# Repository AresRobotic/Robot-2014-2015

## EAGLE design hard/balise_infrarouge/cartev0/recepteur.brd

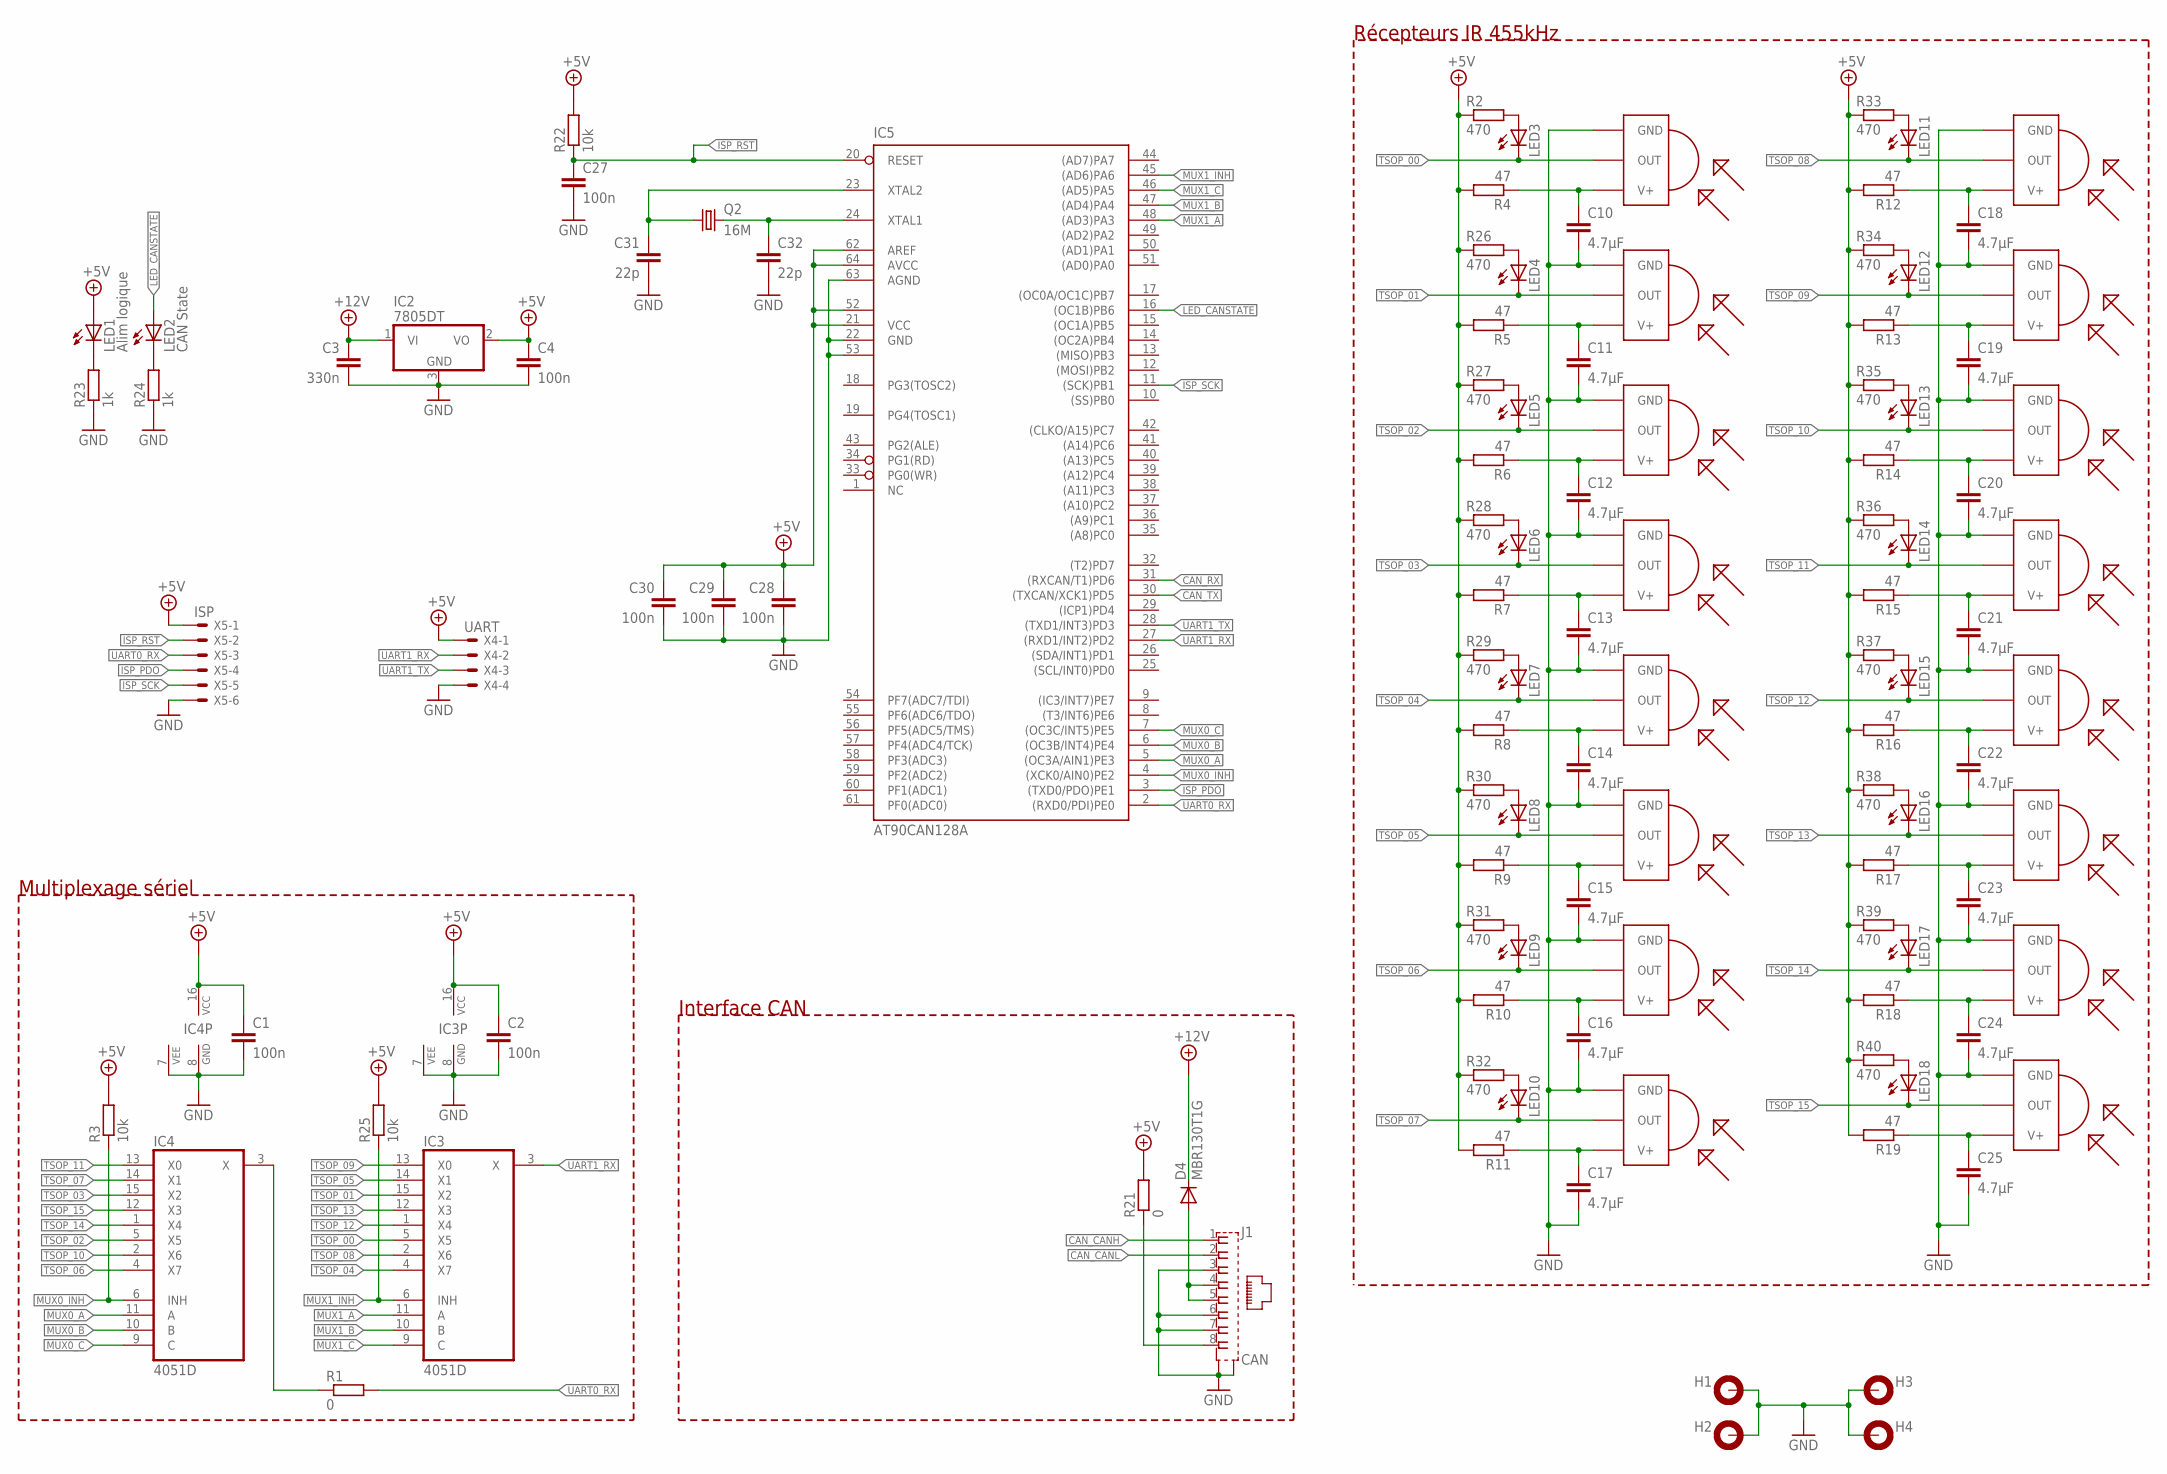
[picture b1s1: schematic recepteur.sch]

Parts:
C1, C2, C4, C27, C28, C29, C30: 100n; C0805
C3: 330n; C0805
C10, C11, C12, C13, C14, C15, C16, C17, C18, C19, C20, C21, C22, C23, C24, C25: 4.7µF; C0805
C31, C32: 22p; C0805
D4: MBR130T1G; SOD123
H1, H2, H3, H4: MOUNT-PAD-ROUND3.0; 3,0-PAD
IC2: 7805DT; TO252
IC3, IC4: 4051D; SO16
IC5: AT90CAN128A; TQFP64
J1: CAN; 557969-1
LED1: Alim logique; CHIP-LED0805
LED2: CAN State; CHIP-LED0805
LED3, LED4, LED5, LED6, LED7, LED8, LED9, LED10, LED11, LED12, LED13, LED14, LED15, LED16, LED17, LED18: LEDCHIP-LED0805; CHIP-LED0805
Q2: 16M; HC49UP
R1: 0; R0805
R2, R26, R27, R28, R29, R30, R31, R32, R33, R34, R35, R36, R37, R38, R39, R40: 470; R0805
R3, R22, R25: 10k; R0805
R4, R5, R6, R7, R8, R9, R10, R11, R12, R13, R14, R15, R16, R17, R18, R19: 47; R0805
R21: 0; M0805
R23, R24: 1k; M0805
TSOP00, TSOP01, TSOP02, TSOP03, TSOP04, TSOP05, TSOP06, TSOP07, TSOP08, TSOP09, TSOP10, TSOP11, TSOP12, TSOP13, TSOP14, TSOP15: TSOP7000; TSOP18XX
X4: UART; 53261-04
X5: ISP; 53261-06

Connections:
+5V: C1.1, C2.1, C4.1, C28.1, C29.1, C30.1, IC2.2 (VO), IC3.16 (VCC), IC4.16 (VCC), IC5.21 (VCC), IC5.52 (VCC1), IC5.62 (AREF), IC5.64 (AVCC), LED1.A, R2.1, R3.2, R4.2, R5.2, R6.2, R7.2, R8.2, R9.2, R10.2, R11.2, R12.2, R13.2, R14.2, R15.2, R16.2, R17.2, R18.2, R19.2, R21.2, R22.2, R25.2, R26.1, R27.1, R28.1, R29.1, R30.1, R31.1, R32.1, R33.1, R34.1, R35.1, R36.1, R37.1, R38.1, R39.1, R40.1, X4.1, X5.1
+12V: C3.1, D4.C, IC2.1 (VI)
CAN_CANH: J1.1
CAN_CANL: J1.2
CAN_RX: IC5.31 ((RXCAN/T1)PD6)
CAN_TX: IC5.30 ((TXCAN/XCK1)PD5)
GND: C1.2, C2.2, C3.2, C4.2, C10.2, C11.2, C12.2, C13.2, C14.2, C15.2, C16.2, C17.2, C18.2, C19.2, C20.2, C21.2, C22.2, C23.2, C24.2, C25.2, C27.2, C28.2, C29.2, C30.2, C31.2, C32.2, H1.B3,0, H2.B3,0, H3.B3,0, H4.B3,0, IC2.3 (GND), IC3.7 (VEE), IC3.8 (GND), IC4.7 (VEE), IC4.8 (GND), IC5.22 (GND), IC5.53 (GND1), IC5.63 (AGND), J1.3, J1.6, J1.7, J1.G1 (S2), J1.G2 (S1), R23.1, R24.1, TSOP00.GND, TSOP01.GND, TSOP02.GND, TSOP03.GND, TSOP04.GND, TSOP05.GND, TSOP06.GND, TSOP07.GND, TSOP08.GND, TSOP09.GND, TSOP10.GND, TSOP11.GND, TSOP12.GND, TSOP13.GND, TSOP14.GND, TSOP15.GND, X4.4, X5.6
ISP_PDO: IC5.3 ((TXD0/PDO)PE1), X5.4
ISP_RST: C27.1, IC5.20 (RESET), R22.1, X5.2
ISP_SCK: IC5.11 ((SCK)PB1), X5.5
LED_CANSTATE: IC5.16 ((OC1B)PB6), LED2.A
MUX0_A: IC4.11 (A), IC5.5 ((OC3A/AIN1)PE3)
MUX0_B: IC4.10 (B), IC5.6 ((OC3B/INT4)PE4)
MUX0_C: IC4.9 (C), IC5.7 ((OC3C/INT5)PE5)
MUX0_INH: IC4.6 (INH), IC5.4 ((XCK0/AIN0)PE2), R3.1
MUX1_A: IC3.11 (A), IC5.48 ((AD3)PA3)
MUX1_B: IC3.10 (B), IC5.47 ((AD4)PA4)
MUX1_C: IC3.9 (C), IC5.46 ((AD5)PA5)
MUX1_INH: IC3.6 (INH), IC5.45 ((AD6)PA6), R25.1
unnamed: IC4.3 (X), R1.1
unnamed: LED3.A, R2.2
unnamed: LED4.A, R26.2
unnamed: LED5.A, R27.2
unnamed: LED6.A, R28.2
unnamed: LED7.A, R29.2
unnamed: J1.8, R21.1
unnamed: C10.1, R4.1, TSOP00.VCC (V+)
unnamed: C11.1, R5.1, TSOP01.VCC (V+)
unnamed: C12.1, R6.1, TSOP02.VCC (V+)
unnamed: C13.1, R7.1, TSOP03.VCC (V+)
unnamed: C32.1, IC5.24 (XTAL1), Q2.2
unnamed: C31.1, IC5.23 (XTAL2), Q2.1
unnamed: LED1.C, R23.2
unnamed: LED8.A, R30.2
unnamed: LED2.C, R24.2
unnamed: LED9.A, R31.2
unnamed: LED10.A, R32.2
unnamed: LED11.A, R33.2
unnamed: C14.1, R8.1, TSOP04.VCC (V+)
unnamed: C15.1, R9.1, TSOP05.VCC (V+)
unnamed: C16.1, R10.1, TSOP06.VCC (V+)
unnamed: LED12.A, R34.2
unnamed: LED13.A, R35.2
unnamed: LED14.A, R36.2
unnamed: LED15.A, R37.2
unnamed: LED16.A, R38.2
unnamed: LED17.A, R39.2
unnamed: LED18.A, R40.2
unnamed: C17.1, R11.1, TSOP07.VCC (V+)
unnamed: C25.1, R19.1, TSOP15.VCC (V+)
unnamed: D4.A, J1.4, J1.5
unnamed: C24.1, R18.1, TSOP14.VCC (V+)
unnamed: C23.1, R17.1, TSOP13.VCC (V+)
unnamed: C22.1, R16.1, TSOP12.VCC (V+)
unnamed: C21.1, R15.1, TSOP11.VCC (V+)
unnamed: C19.1, R13.1, TSOP09.VCC (V+)
unnamed: C20.1, R14.1, TSOP10.VCC (V+)
unnamed: C18.1, R12.1, TSOP08.VCC (V+)
TSOP_00: IC3.5 (X5), LED3.C, TSOP00.OUT
TSOP_01: IC3.15 (X2), LED4.C, TSOP01.OUT
TSOP_02: IC4.5 (X5), LED5.C, TSOP02.OUT
TSOP_03: IC4.15 (X2), LED6.C, TSOP03.OUT
TSOP_04: IC3.4 (X7), LED7.C, TSOP04.OUT
TSOP_05: IC3.14 (X1), LED8.C, TSOP05.OUT
TSOP_06: IC4.4 (X7), LED9.C, TSOP06.OUT
TSOP_07: IC4.14 (X1), LED10.C, TSOP07.OUT
TSOP_08: IC3.2 (X6), LED11.C, TSOP08.OUT
TSOP_09: IC3.13 (X0), LED12.C, TSOP09.OUT
TSOP_10: IC4.2 (X6), LED13.C, TSOP10.OUT
TSOP_11: IC4.13 (X0), LED14.C, TSOP11.OUT
TSOP_12: IC3.1 (X4), LED15.C, TSOP12.OUT
TSOP_13: IC3.12 (X3), LED16.C, TSOP13.OUT
TSOP_14: IC4.1 (X4), LED17.C, TSOP14.OUT
TSOP_15: IC4.12 (X3), LED18.C, TSOP15.OUT
UART0_RX: IC5.2 ((RXD0/PDI)PE0), R1.2, X5.3
UART1_RX: IC3.3 (X), IC5.27 ((RXD1/INT2)PD2), X4.2
UART1_TX: IC5.28 ((TXD1/INT3)PD3), X4.3

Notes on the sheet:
Interface CAN
Multiplexage sériel
Récepteurs IR 455kHz

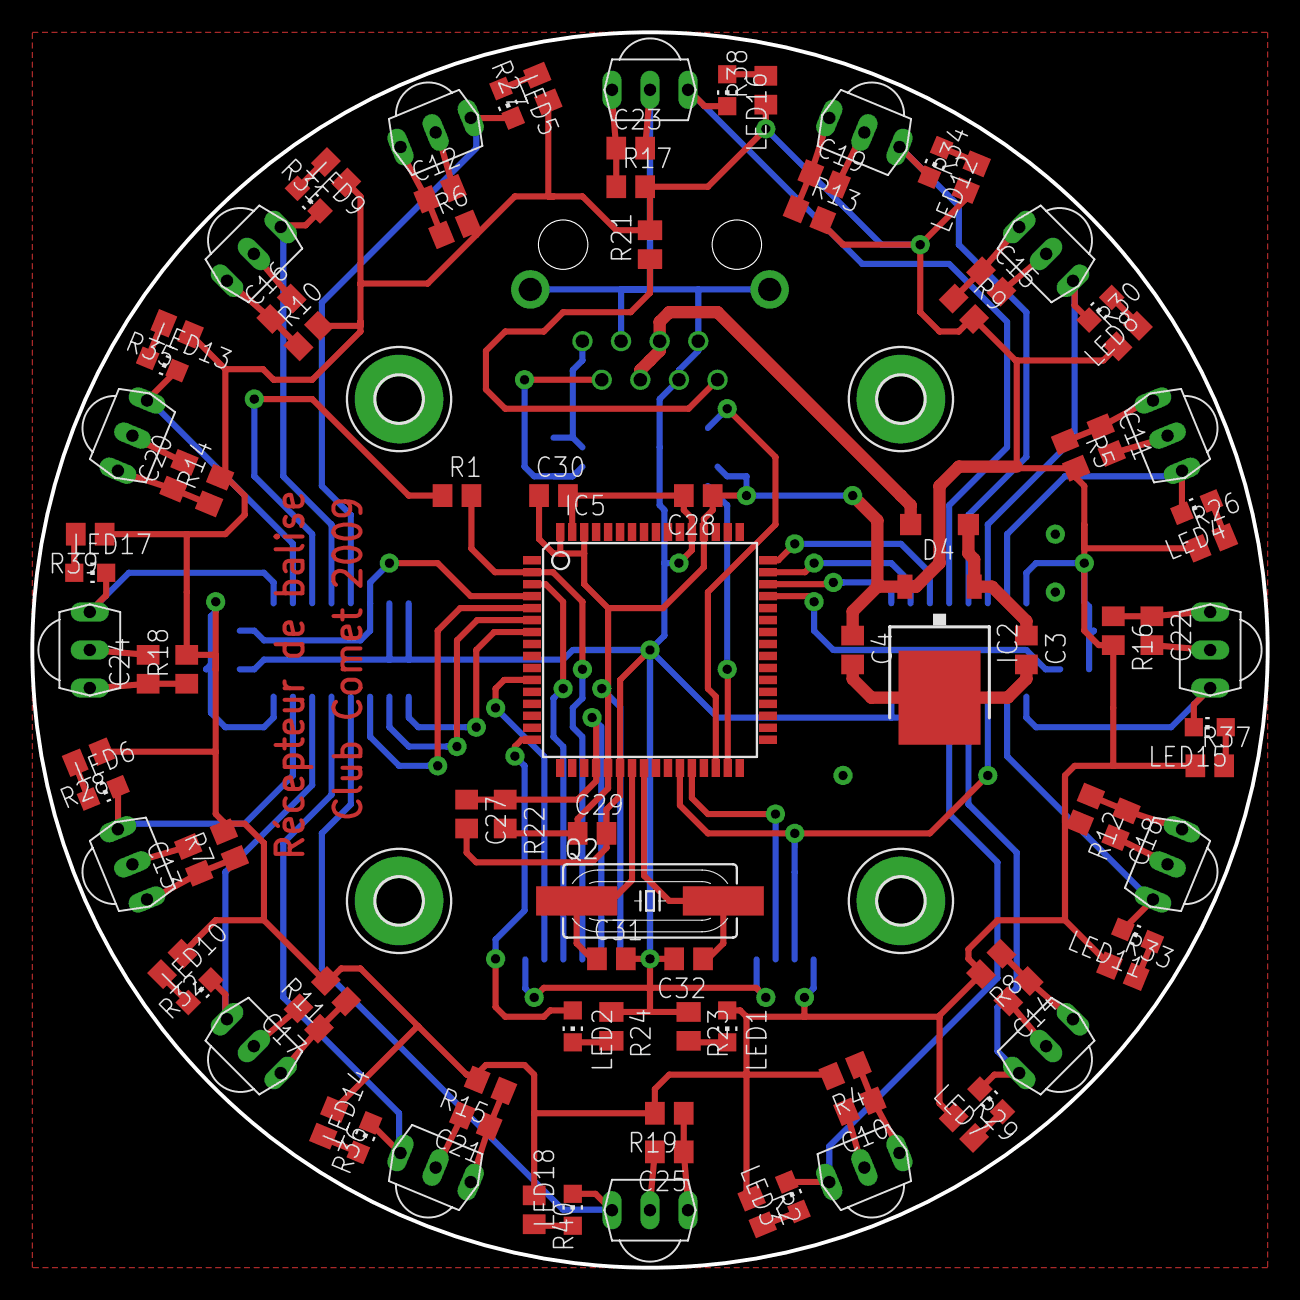
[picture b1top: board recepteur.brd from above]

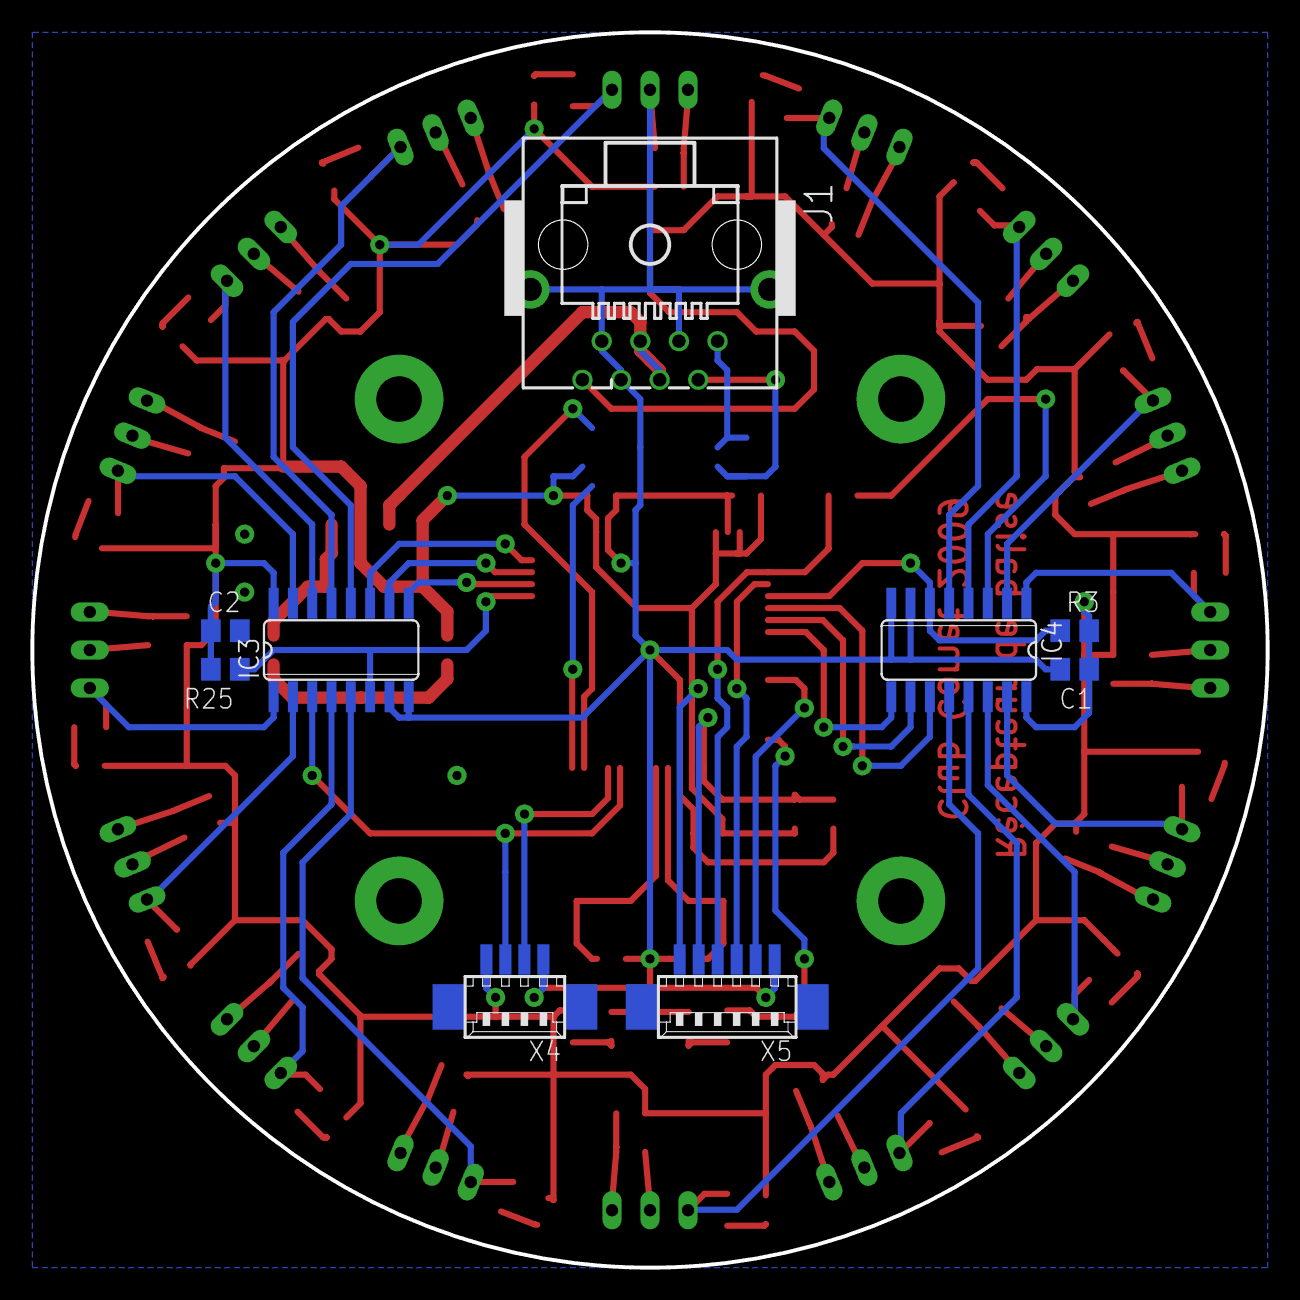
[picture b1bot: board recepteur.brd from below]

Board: 2 copper layers, 81.3 x 81.3 mm, 112 parts (9 on the bottom side), 73 nets.

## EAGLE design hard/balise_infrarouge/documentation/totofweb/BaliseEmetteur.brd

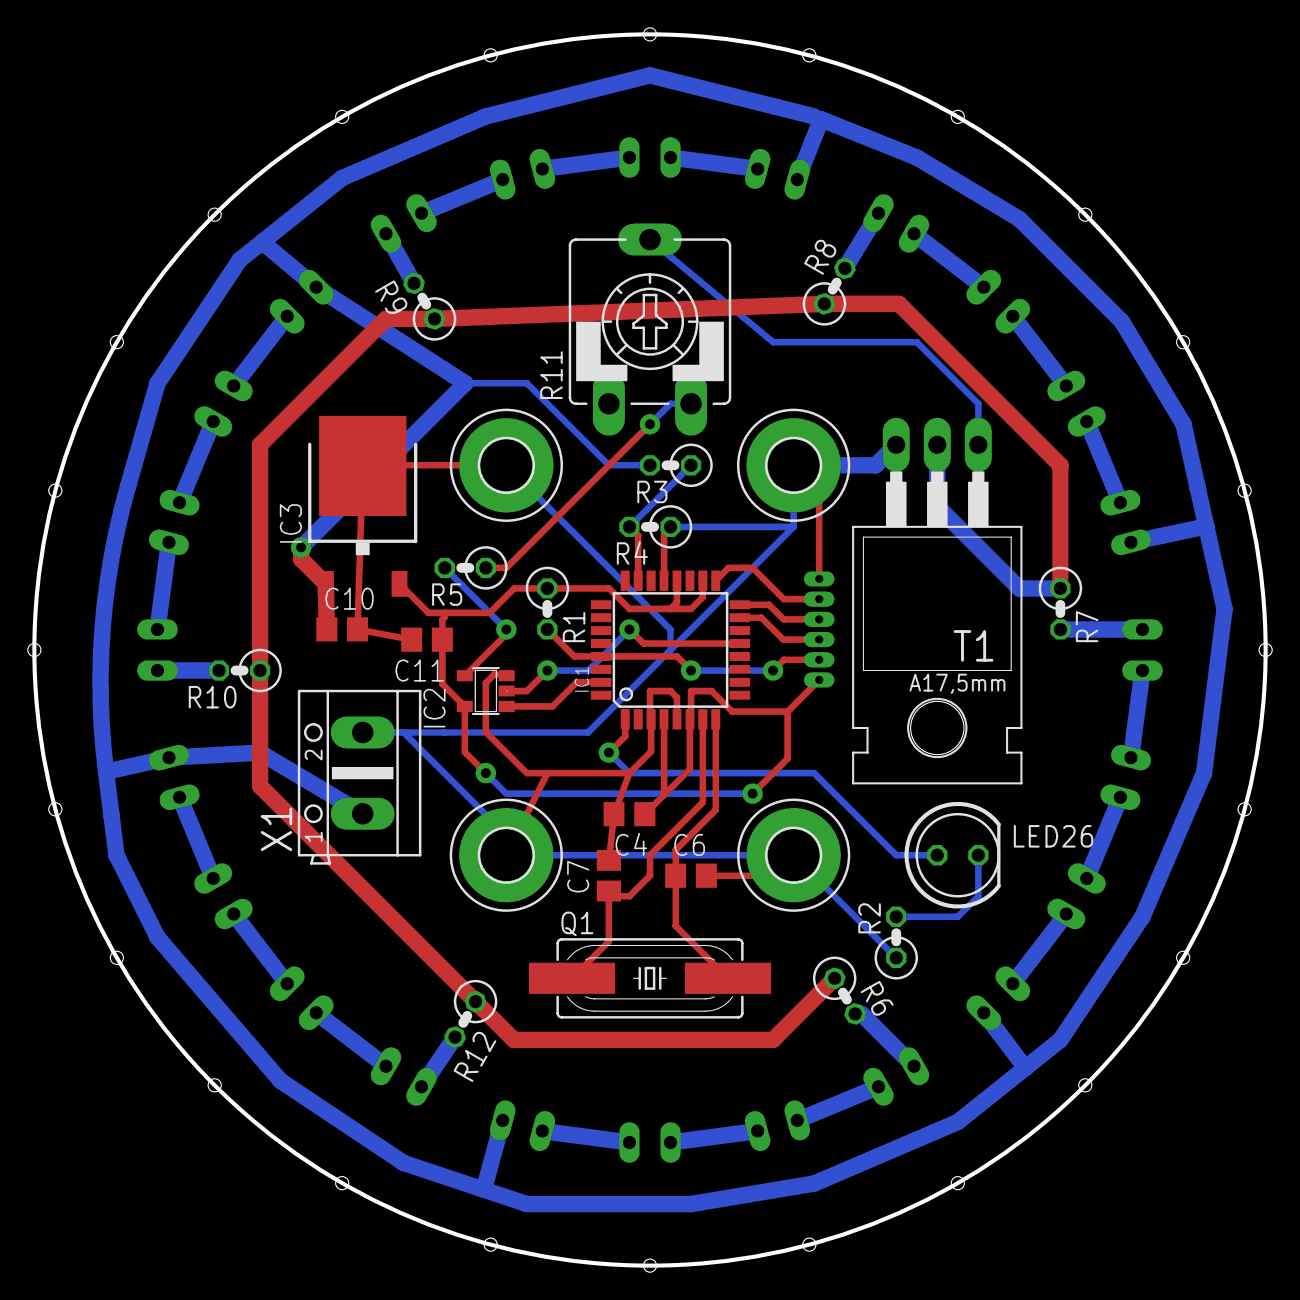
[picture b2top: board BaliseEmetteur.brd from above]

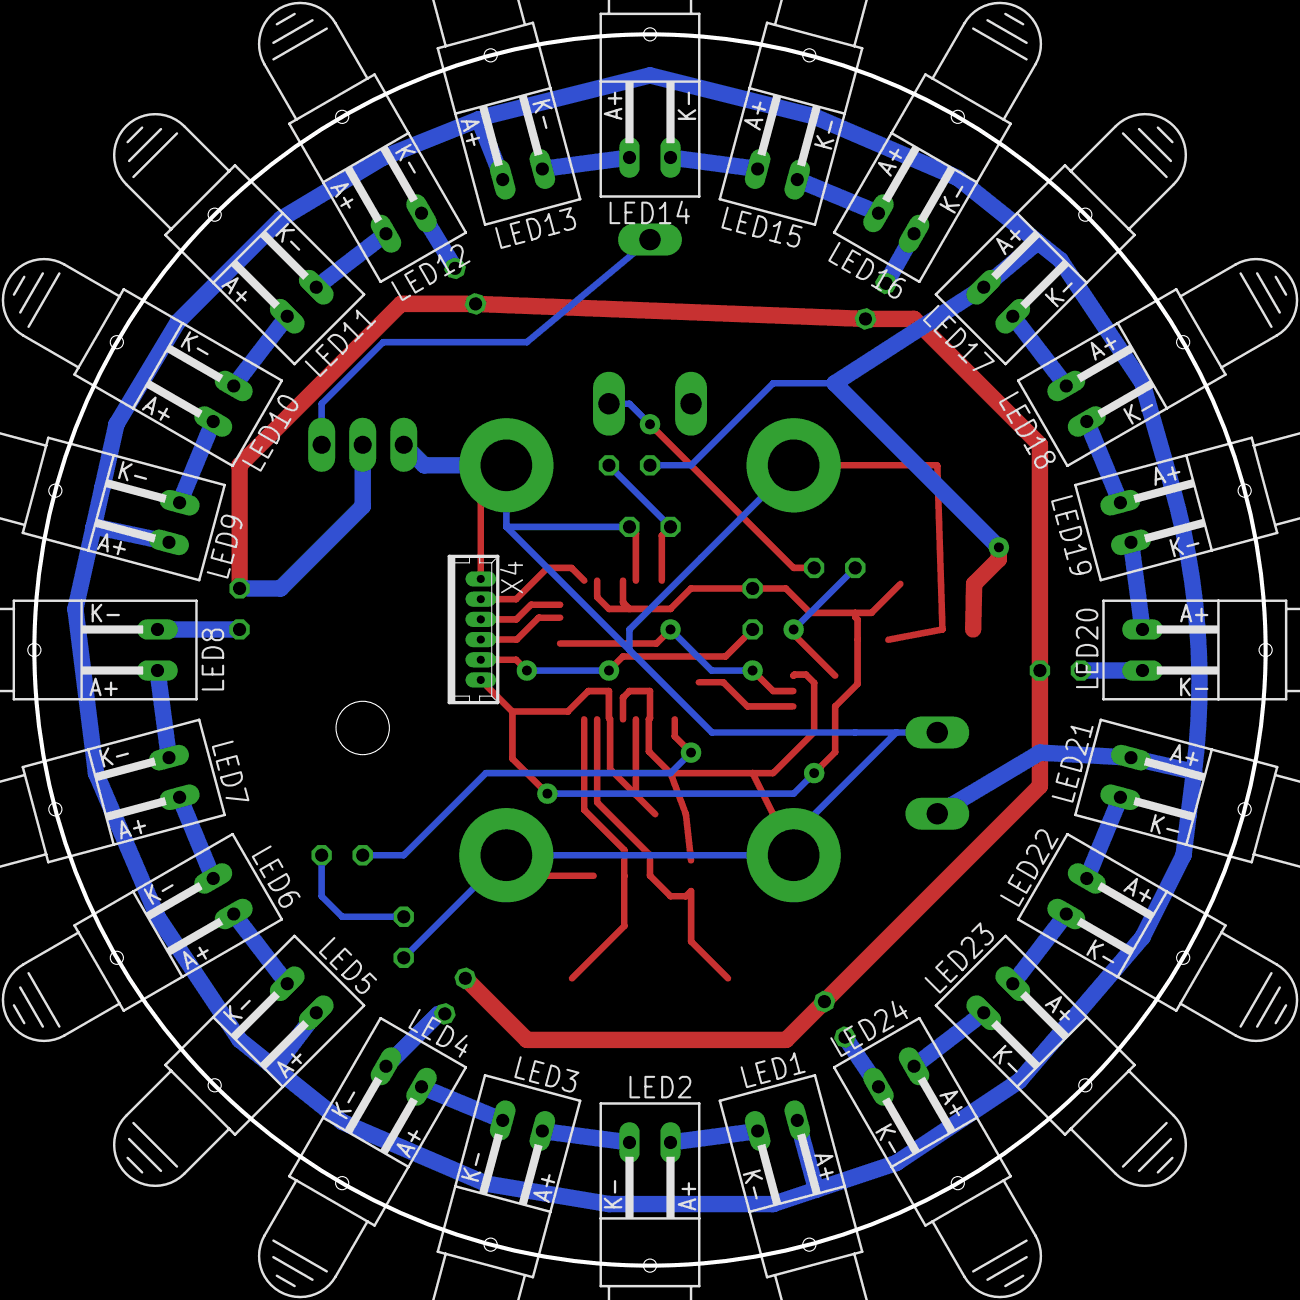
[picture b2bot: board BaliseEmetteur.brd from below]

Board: 2 copper layers, 76.2 x 76.2 mm, 53 parts (25 on the bottom side), 42 nets.

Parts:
C4: 100nF; C0805
C6, C7: 22pF; C0805
C10: 330n; C0805
C11: 100n; C0805
H1, H2, H3, H4: 3,2-PAD
IC1: MEGA8-AI; TQFP32-08
IC2: 74AHC1G02DBV; SOT23-5
IC3: 7805DT; TO252
LED1, LED2, LED3, LED4, LED5, LED6, LED7, LED8, LED9, LED10, LED11, LED12, LED13, LED14, LED15, LED16, LED17, LED18, LED19, LED20, LED21, LED22, LED23, LED24: Q62902-B155
LED26: LED5MM
Q1: 16MHz; HC49UP
R1, R3, R4: 10k; 0207/2V
R2: 470; 0207/2V
R5: 4k7; 0207/2V
R6, R7, R8, R9, R10, R12: 10; 0207/2V
R11: 220k; CA9V
T1: TIP122; TO220
X1: ALIM; AK500/2
X4: ISP; 53047-06

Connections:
+5V: C4.1, C11.1, IC1.4, IC1.6, IC1.18, IC1.20, IC2.5, IC3.2, R1.1, X4.1
+12V: C10.1, IC3.1, LED1.A, LED5.A, LED9.A, LED13.A, LED17.A, LED21.A, R3.2, X1.1
BATT_ADC: IC1.23, R3.1, R4.2
GND: C4.2, C6.2, C7.2, C10.2, C11.2, H1.B3,2, H2.B3,2, H3.B3,2, H4.B3,2, IC1.3, IC1.5, IC1.21, IC2.3, IC3.3, R2.1, R4.1, T1.3, X1.2, X4.6
ISP_MISO: IC1.16, X4.4
ISP_MOSI: IC1.15, X4.3
ISP_RST: IC1.29, R1.2, X4.2
ISP_SCK: IC1.17, X4.5
unnamed: LED26.K, R2.2
unnamed: LED1.K, LED2.A
unnamed: R5.1, R11.E
unnamed: IC1.1, LED26.A
unnamed: LED3.K, LED4.A
unnamed: LED6.K, LED7.A
unnamed: LED5.K, LED6.A
unnamed: C7.1, IC1.7, Q1.1
unnamed: C6.1, IC1.8, Q1.2
unnamed: LED7.K, LED8.A
unnamed: LED18.K, LED19.A
unnamed: LED9.K, LED10.A
unnamed: LED2.K, LED3.A
unnamed: LED11.K, LED12.A
unnamed: LED13.K, LED14.A
unnamed: R6.1, R7.1, R8.1, R9.1, R10.1, R12.1, T1.2
unnamed: LED15.K, LED16.A
unnamed: LED22.K, LED23.A
unnamed: LED17.K, LED18.A
unnamed: LED19.K, LED20.A
unnamed: LED4.K, R6.2
unnamed: LED21.K, LED22.A
unnamed: LED10.K, LED11.A
unnamed: LED23.K, LED24.A
unnamed: LED8.K, R7.2
unnamed: LED14.K, LED15.A
unnamed: LED12.K, R8.2
unnamed: LED16.K, R9.2
unnamed: R11.S, T1.1
unnamed: LED20.K, R10.2
unnamed: LED24.K, R12.2
unnamed: IC2.4, R5.2
PWM: IC1.13, IC2.2
UART_TX: IC1.31, IC2.1

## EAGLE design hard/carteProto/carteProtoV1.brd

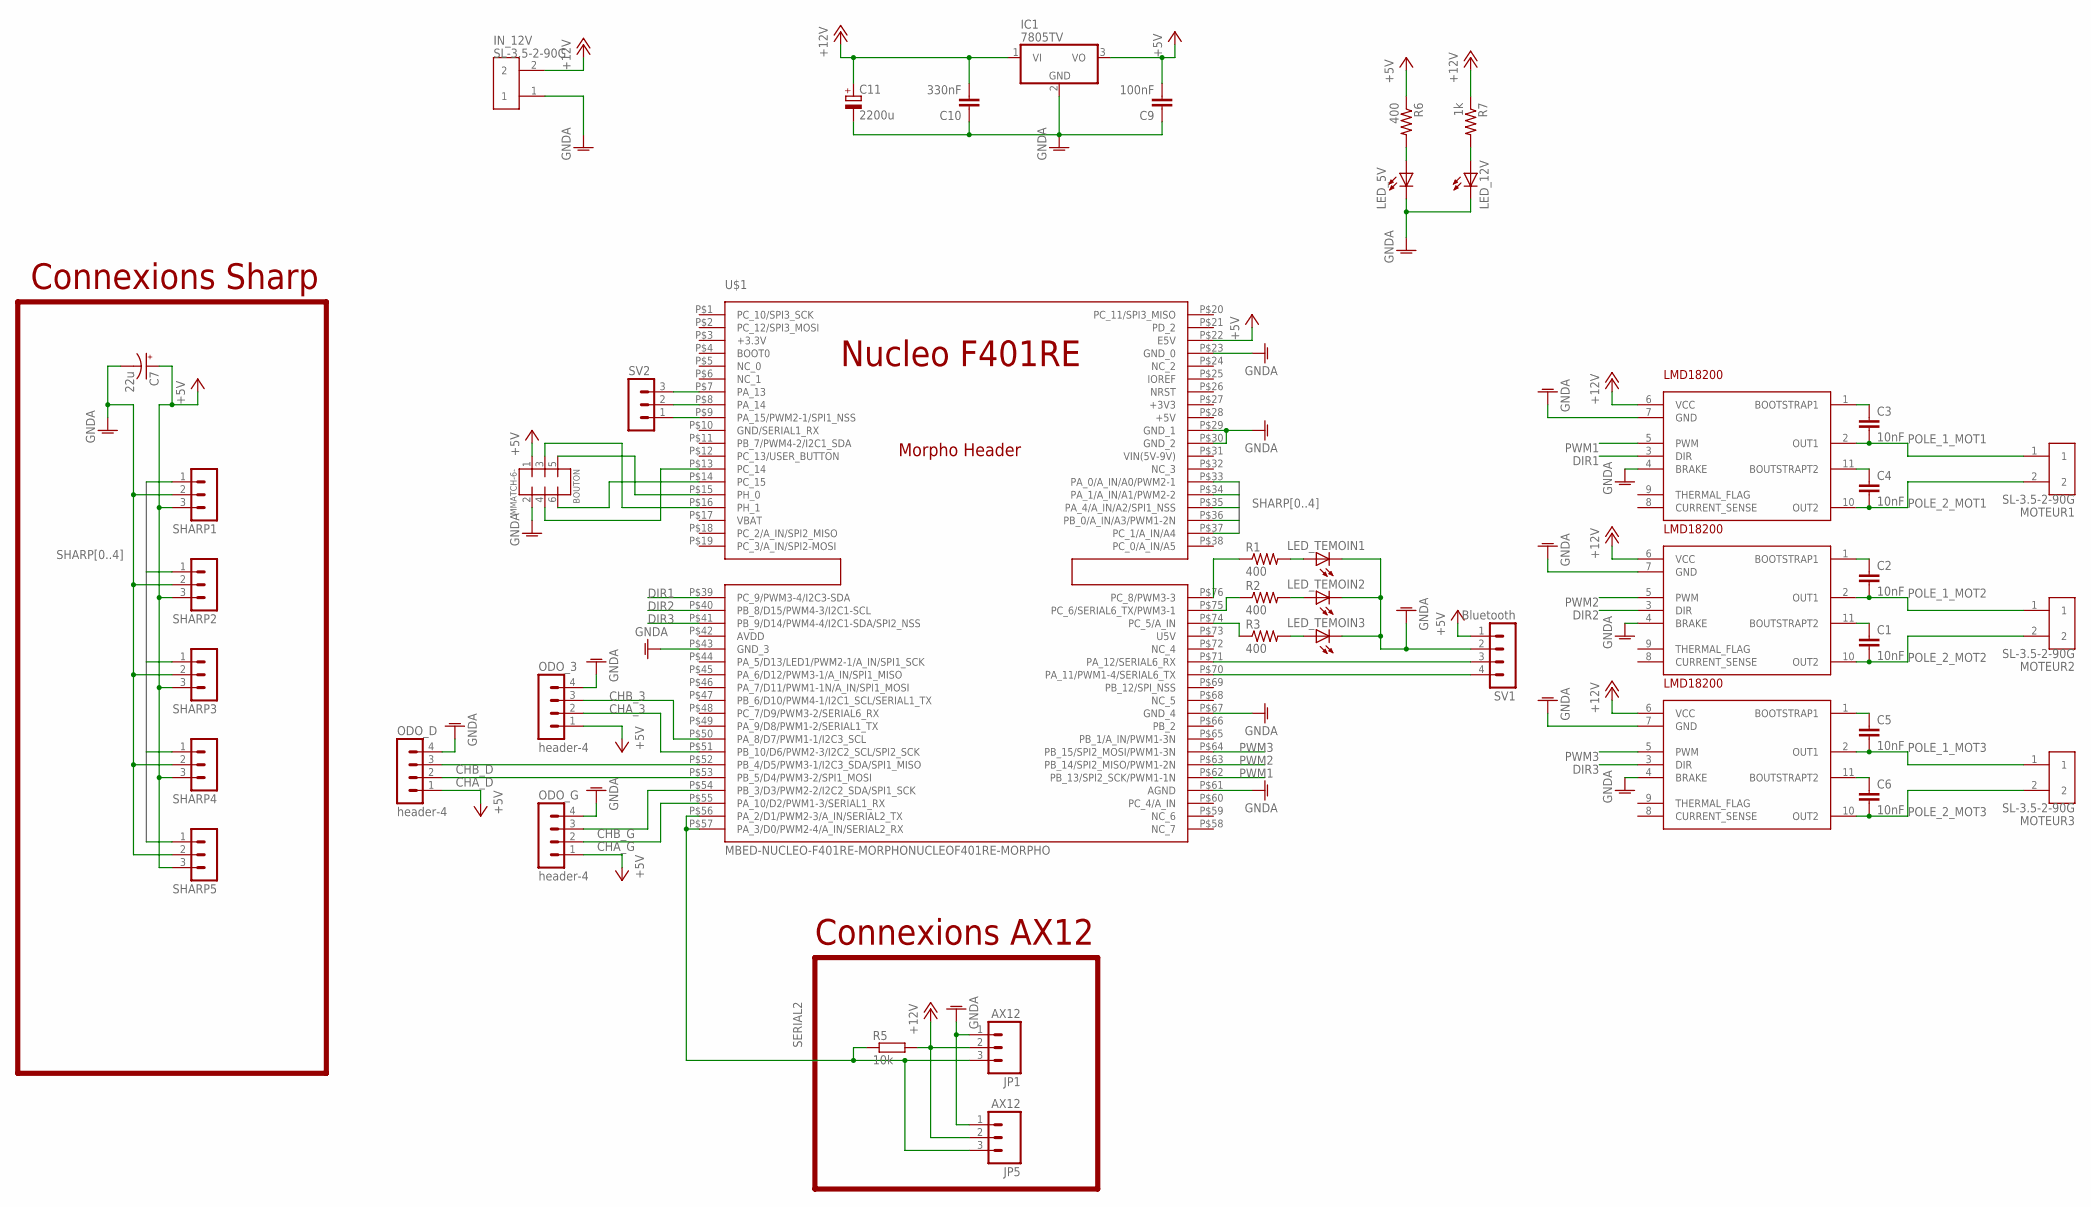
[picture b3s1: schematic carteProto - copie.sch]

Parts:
BOUTON: MMATCH-6-; AMP-215079-6
C1, C2, C3, C4, C5, C6: 10nF; C0805
C7: 22u; CPOL-RADIAL-100UF-25V
C9: 100nF; C0805
C10: 330nF; C0805
C11: 2200u; TT5D11
IC1: 7805TV; TO220V
IN_12V: SL-3.5-2-90G
JP1, JP5: AX12; MOLEX-1X3
LED_5V, LED_12V: LEDCHIPLED_0805; CHIPLED_0805
LED_TEMOIN1, LED_TEMOIN2, LED_TEMOIN3: LEDCHIPLED_0805; CHIPLED_0805
MOTEUR1, MOTEUR2, MOTEUR3: SL-3.5-2-90G
ODO_3: header-4; MA04-1
ODO_D: header-4; MA04-1
ODO_G: header-4; MA04-1
R1, R2, R3, R6: 400; 0805
R5: 10k; M0805
R7: 1k; 0805
SHARP1, SHARP2, SHARP3, SHARP4, SHARP5: MA03-1
SV1: Bluetooth; MA04-1
SV2: MA03-1
U$1: MBED-NUCLEO-F401RE-MORPHONUCLEOF401RE-MORPHO; MORPHO-HEADERS
U$2, U$3, U$4: LMD18200

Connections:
+5V: BOUTON.1 (3), C7.1 (+), C9.2, IC1.3 (VO), ODO_3.1, ODO_D.1, ODO_G.1, R6.1, SHARP1.3, SHARP2.3, SHARP3.3, SHARP4.3, SHARP5.3, SV1.1, U$1.P$22 (E5V); also elsewhere on the board
CHA_3: ODO_3.2, U$1.P$51 (PB_10/D6/PWM2-3/I2C2_SCL/SPI2_SCK)
CHA_D: ODO_D.2, U$1.P$53 (PB_5/D4/PWM3-2/SPI1_MOSI)
CHA_G: ODO_G.2, U$1.P$55 (PA_10/D2/PWM1-3/SERIAL1_RX)
CHB_3: ODO_3.3, U$1.P$50 (PA_8/D7/PWM1-1/I2C3_SCL)
CHB_D: ODO_D.3, U$1.P$52 (PB_4/D5/PWM3-1/I2C3_SDA/SPI1_MISO)
CHB_G: ODO_G.3, U$1.P$54 (PB_3/D3/PWM2-2/I2C2_SDA/SPI1_SCK)
DIR1: U$1.P$39 (PC_9/PWM3-4/I2C3-SDA), U$2.3 (DIR)
DIR2: U$1.P$40 (PB_8/D15/PWM4-3/I2C1-SCL), U$3.3 (DIR)
DIR3: U$1.P$41 (PB_9/D14/PWM4-4/I2C1-SDA/SPI2_NSS), U$4.3 (DIR)
GNDA: BOUTON.2 (4), C7.2 (-), C9.1, C10.1, C11.-, IC1.2 (GND), IN_12V.1, JP1.1, JP5.1, LED_5V.C, LED_12V.C, LED_TEMOIN1.C, LED_TEMOIN2.C, LED_TEMOIN3.C, ODO_3.4, ODO_D.4, ODO_G.4, SHARP1.2, SHARP2.2, SHARP3.2, SHARP4.2, SHARP5.2, SV1.2, U$1.P$23 (GND_0), U$1.P$29 (GND_1), U$1.P$30 (GND_2), U$1.P$43 (GND_3), U$1.P$61 (AGND), U$1.P$67 (GND_4), U$2.4 (BRAKE), U$2.7 (GND), U$3.4 (BRAKE), U$3.7 (GND), U$4.4 (BRAKE), U$4.7 (GND); also elsewhere on the board
unnamed: C1.1, U$3.11 (BOUTSTRAPT2)
unnamed: C5.1, U$4.1 (BOOTSTRAP1)
unnamed: C2.1, U$3.1 (BOOTSTRAP1)
unnamed: C6.1, U$4.11 (BOUTSTRAPT2)
unnamed: C3.1, U$2.1 (BOOTSTRAP1)
unnamed: SV1.3, U$1.P$71 (PA_12/SERIAL6_RX)
unnamed: C4.1, U$2.11 (BOUTSTRAPT2)
unnamed: SV1.4, U$1.P$70 (PA_11/PWM1-4/SERIAL6_TX)
unnamed: LED_5V.A, R6.2
unnamed: LED_TEMOIN3.A, R3.2
unnamed: LED_12V.A, R7.2
unnamed: R1.1, U$1.P$76 (PC_8/PWM3-3)
unnamed: R2.1, U$1.P$75 (PC_6/SERIAL6_TX/PWM3-1)
unnamed: R3.1, U$1.P$74 (PC_5/A_IN)
unnamed: LED_TEMOIN1.A, R1.2
unnamed: LED_TEMOIN2.A, R2.2
unnamed: BOUTON.3 (5), U$1.P$16 (PH_1)
unnamed: BOUTON.5 (7), U$1.P$15 (PH_0)
unnamed: BOUTON.6 (8), U$1.P$14 (PC_15)
unnamed: BOUTON.4 (6), U$1.P$13 (PC_14)
unnamed: SV2.3, U$1.P$7 (PA_13)
unnamed: SV2.2, U$1.P$8 (PA_14)
unnamed: SV2.1, U$1.P$9 (PA_15/PWM2-1/SPI1_NSS)
POLE_1_MOT1: C3.2, MOTEUR1.1, U$2.2 (OUT1)
POLE_1_MOT2: C2.2, MOTEUR2.1, U$3.2 (OUT1)
POLE_1_MOT3: C5.2, MOTEUR3.1, U$4.2 (OUT1)
POLE_2_MOT1: C4.2, MOTEUR1.2, U$2.10 (OUT2)
POLE_2_MOT2: C1.2, MOTEUR2.2, U$3.10 (OUT2)
POLE_2_MOT3: C6.2, MOTEUR3.2, U$4.10 (OUT2)
PWM1: U$1.P$62 (PB_13/SPI2_SCK/PWM1-1N), U$2.5 (PWM)
PWM2: U$1.P$63 (PB_14/SPI2_MISO/PWM1-2N), U$3.5 (PWM)
PWM3: U$1.P$64 (PB_15/SPI2_MOSI/PWM1-3N), U$4.5 (PWM)
SERIAL2: JP1.3, JP5.3, R5.1, U$1.P$56 (PA_2/D1/PWM2-3/A_IN/SERIAL2_TX), U$1.P$57 (PA_3/D0/PWM2-4/A_IN/SERIAL2_RX); also elsewhere on the board
SHARP0: SHARP1.1, U$1.P$33 (PA_0/A_IN/A0/PWM2-1)
SHARP1: SHARP2.1, U$1.P$34 (PA_1/A_IN/A1/PWM2-2)
SHARP2: SHARP3.1, U$1.P$35 (PA_4/A_IN/A2/SPI1_NSS)
SHARP3: SHARP4.1, U$1.P$36 (PB_0/A_IN/A3/PWM1-2N)
SHARP4: SHARP5.1, U$1.P$37 (PC_1/A_IN/A4)

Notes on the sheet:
Connexions Sharp
Connexions AX12

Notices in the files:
parts and their libraries:
SparkFun-Capacitors: Licensing: CC v3.0 Share-Alike You are welcome to use this library for commercial purposes.
microbuilder: This work is placed in the public domain, and may be freely used for commercial and non-commercial work with the following conditions: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
